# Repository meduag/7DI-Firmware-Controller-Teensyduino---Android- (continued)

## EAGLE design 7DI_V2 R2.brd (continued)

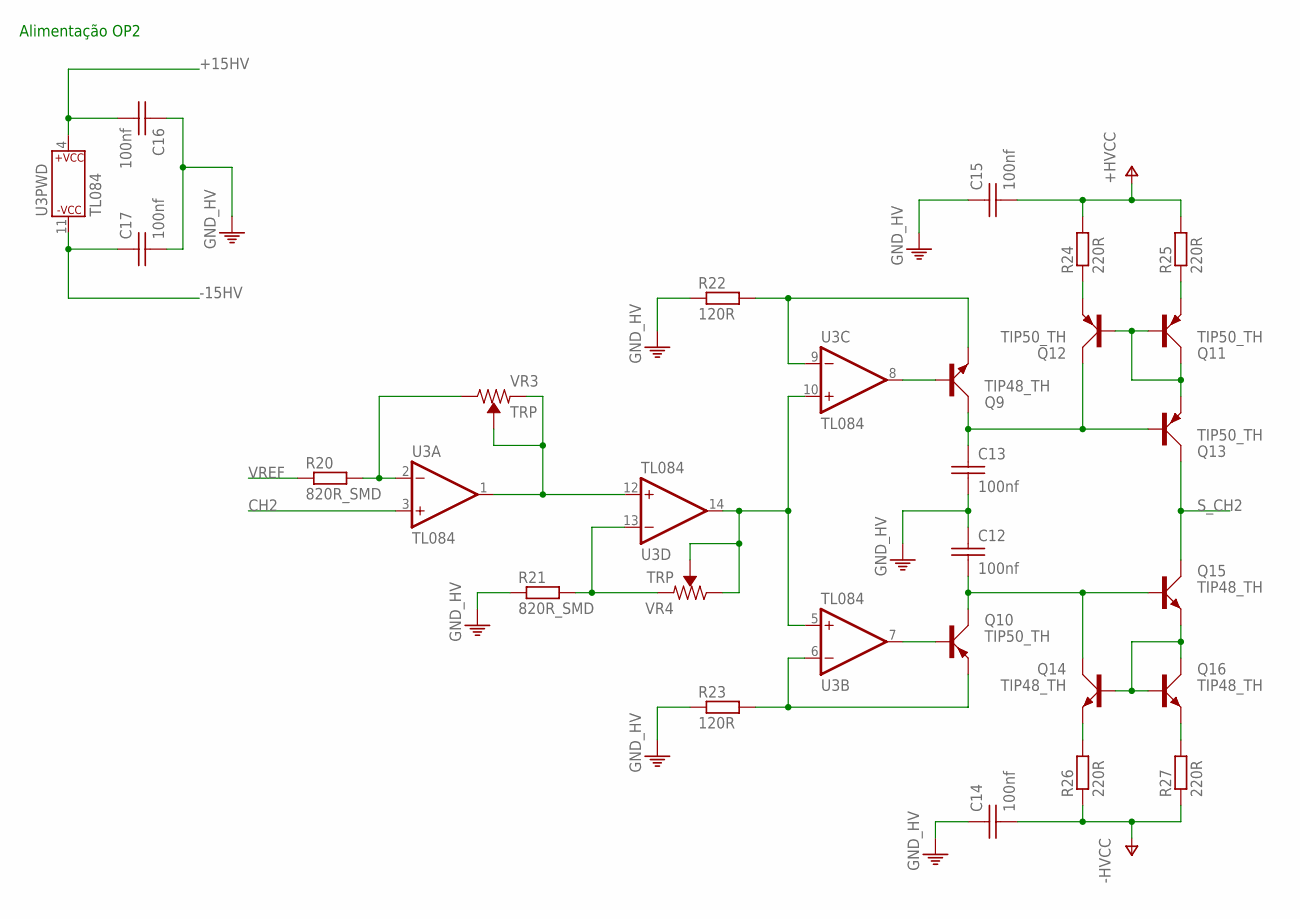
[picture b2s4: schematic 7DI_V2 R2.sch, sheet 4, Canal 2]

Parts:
C12, C13: 100nf; CAP_CER_2,54-5X5
C14, C15: 100nf; CAP_CER_16X7
C16, C17: 100nf; CAP_CER_SMD-0805
Q9, Q14, Q15, Q16: TIP48_TH; TO220
Q10, Q11, Q12, Q13: TIP50_TH; TO220
R20, R21: 820R_SMD; RESISTENCIA_0805
R22, R23: 120R; 0204V
R24, R25, R26, R27: 220R; 0204V
U3: TL084; SO14OP
VR3, VR4: TRP; TRIMPOT-PTH-3386U

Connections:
+15HV: C16.2, U3.4 (P$V+); also elsewhere on the board
-15HV: C17.1, U3.11 (P$V-); also elsewhere on the board
CH2: U3.3 (+IN); also elsewhere on the board
unnamed: R20.2, U3.2 (-IN), VR3.3 (CW)
unnamed: U3.1 (OUT), U3.12 (+IN), VR3.1 (CCW), VR3.2 (WIPER)
unnamed: U3.5 (+IN), U3.10 (+IN), U3.14 (OUT), VR4.2 (WIPER), VR4.3 (CW)
unnamed: R21.2, U3.13 (-IN), VR4.1 (CCW)
unnamed: Q9.E, R22.2, U3.9 (-IN)
unnamed: Q10.B, U3.7 (OUT)
unnamed: Q10.E, R23.2, U3.6 (-IN)
unnamed: C12.2, Q10.C, Q14.C, Q15.B
unnamed: C13.1, Q9.C, Q12.C, Q13.B
unnamed: Q12.E, R24.1
unnamed: Q11.E, R25.1
unnamed: Q11.B, Q11.C, Q12.B, Q13.E
unnamed: Q14.B, Q15.E, Q16.B, Q16.C
unnamed: Q14.E, R26.2
unnamed: Q16.E, R27.2
unnamed: Q9.B, U3.8 (OUT)
PE: C12.1, C13.2, C14.1, C15.1, C16.1, C17.2, R21.1, R22.1, R23.1; also elsewhere on the board
S_CH2: Q13.C, Q15.C; also elsewhere on the board
V+: C15.2, R24.2, R25.2; also elsewhere on the board
V-: C14.2, R26.1, R27.1; also elsewhere on the board
VREF: R20.1; also elsewhere on the board

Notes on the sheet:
Alimentação OP2

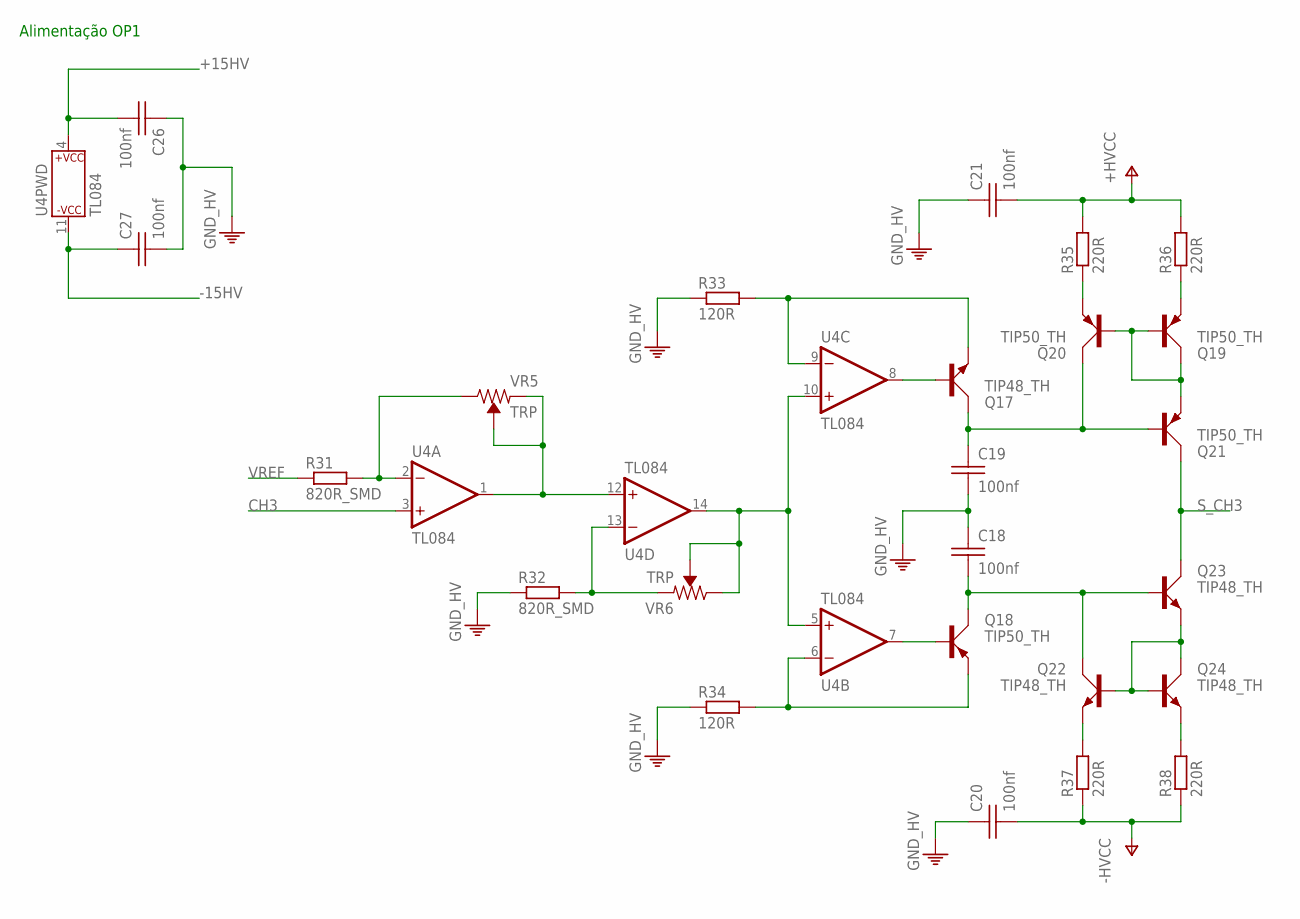
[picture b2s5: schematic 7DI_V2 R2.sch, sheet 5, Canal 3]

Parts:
C18, C19: 100nf; CAP_CER_2,54-5X5
C20, C21: 100nf; CAP_CER_16X7
C26, C27: 100nf; CAP_CER_SMD-0805
Q17, Q22, Q23, Q24: TIP48_TH; TO220
Q18, Q19, Q20, Q21: TIP50_TH; TO220
R31, R32: 820R_SMD; RESISTENCIA_0805
R33, R34: 120R; 0204V
R35, R36, R37, R38: 220R; 0204V
U4: TL084; SO14OP
VR5, VR6: TRP; TRIMPOT-PTH-3386U

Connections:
+15HV: C26.2, U4.4 (P$V+); also elsewhere on the board
-15HV: C27.1, U4.11 (P$V-); also elsewhere on the board
CH3: U4.3 (+IN); also elsewhere on the board
unnamed: R31.2, U4.2 (-IN), VR5.3 (CW)
unnamed: U4.1 (OUT), U4.12 (+IN), VR5.1 (CCW), VR5.2 (WIPER)
unnamed: U4.5 (+IN), U4.10 (+IN), U4.14 (OUT), VR6.2 (WIPER), VR6.3 (CW)
unnamed: R32.2, U4.13 (-IN), VR6.1 (CCW)
unnamed: Q17.E, R33.2, U4.9 (-IN)
unnamed: Q18.B, U4.7 (OUT)
unnamed: Q18.E, R34.2, U4.6 (-IN)
unnamed: C18.2, Q18.C, Q22.C, Q23.B
unnamed: C19.1, Q17.C, Q20.C, Q21.B
unnamed: Q20.E, R35.1
unnamed: Q19.E, R36.1
unnamed: Q19.B, Q19.C, Q20.B, Q21.E
unnamed: Q22.B, Q23.E, Q24.B, Q24.C
unnamed: Q22.E, R37.2
unnamed: Q24.E, R38.2
unnamed: Q17.B, U4.8 (OUT)
PE: C18.1, C19.2, C20.1, C21.1, C26.1, C27.2, R32.1, R33.1, R34.1; also elsewhere on the board
S_CH3: Q21.C, Q23.C; also elsewhere on the board
V+: C21.2, R35.2, R36.2; also elsewhere on the board
V-: C20.2, R37.1, R38.1; also elsewhere on the board
VREF: R31.1; also elsewhere on the board

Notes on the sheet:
Alimentação OP1

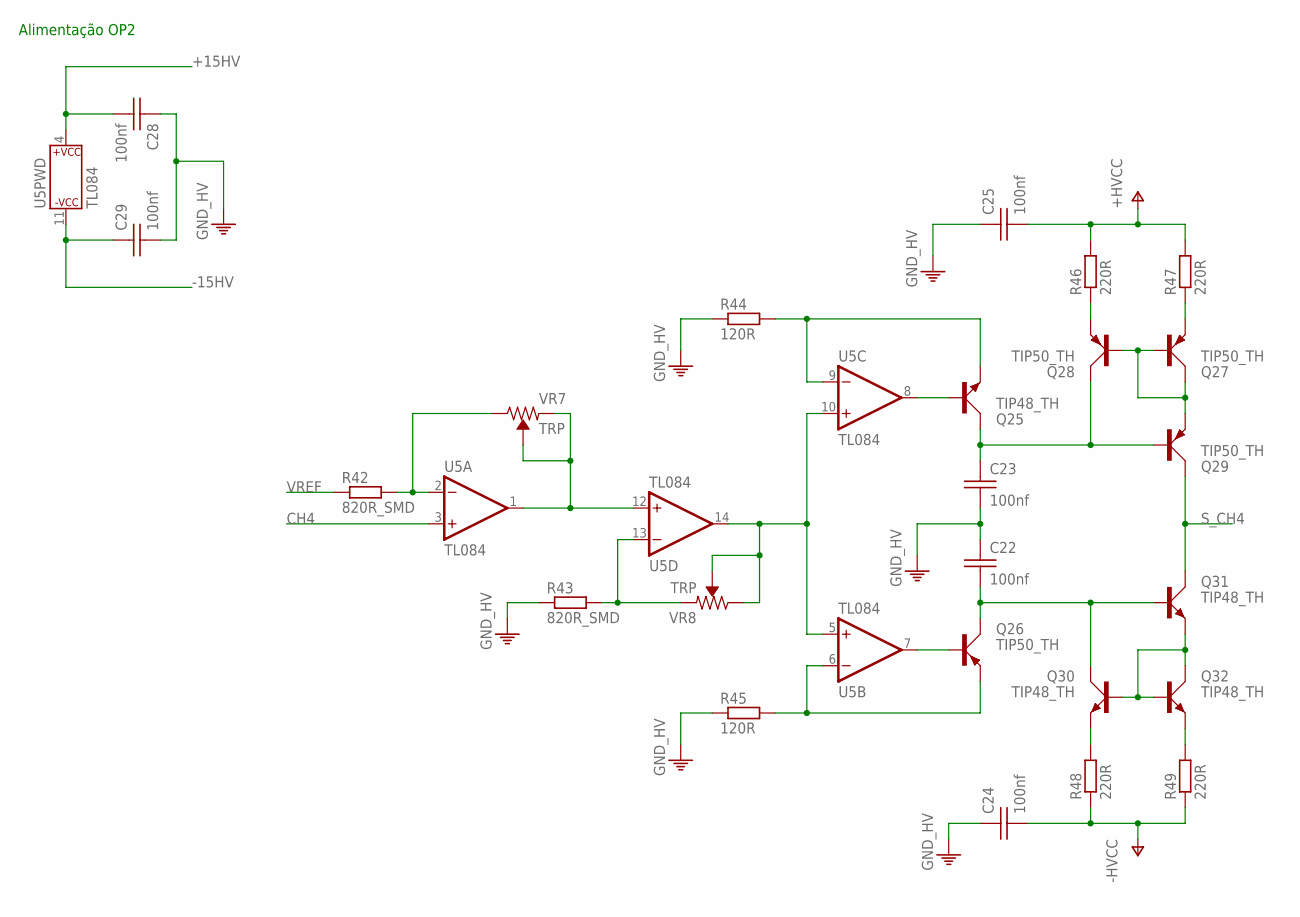
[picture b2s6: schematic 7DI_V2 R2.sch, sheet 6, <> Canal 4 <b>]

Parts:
C22, C23: 100nf; CAP_CER_2,54-5X5
C24, C25: 100nf; CAP_CER_16X7
C28, C29: 100nf; CAP_CER_SMD-0805
Q25, Q30, Q31, Q32: TIP48_TH; TO220
Q26, Q27, Q28, Q29: TIP50_TH; TO220
R42, R43: 820R_SMD; RESISTENCIA_0805
R44, R45: 120R; 0204V
R46, R47, R48, R49: 220R; 0204V
U5: TL084; SO14OP
VR7, VR8: TRP; TRIMPOT-PTH-3386U

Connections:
+15HV: C28.2, U5.4 (P$V+); also elsewhere on the board
-15HV: C29.1, U5.11 (P$V-); also elsewhere on the board
CH4: U5.3 (+IN); also elsewhere on the board
unnamed: R42.2, U5.2 (-IN), VR7.3 (CW)
unnamed: U5.1 (OUT), U5.12 (+IN), VR7.1 (CCW), VR7.2 (WIPER)
unnamed: U5.5 (+IN), U5.10 (+IN), U5.14 (OUT), VR8.2 (WIPER), VR8.3 (CW)
unnamed: R43.2, U5.13 (-IN), VR8.1 (CCW)
unnamed: Q25.E, R44.2, U5.9 (-IN)
unnamed: Q26.B, U5.7 (OUT)
unnamed: Q26.E, R45.2, U5.6 (-IN)
unnamed: C22.2, Q26.C, Q30.C, Q31.B
unnamed: C23.1, Q25.C, Q28.C, Q29.B
unnamed: Q28.E, R46.1
unnamed: Q27.E, R47.1
unnamed: Q27.B, Q27.C, Q28.B, Q29.E
unnamed: Q30.B, Q31.E, Q32.B, Q32.C
unnamed: Q30.E, R48.2
unnamed: Q32.E, R49.2
unnamed: Q25.B, U5.8 (OUT)
PE: C22.1, C23.2, C24.1, C25.1, C28.1, C29.2, R43.1, R44.1, R45.1; also elsewhere on the board
S_CH4: Q29.C, Q31.C; also elsewhere on the board
V+: C25.2, R46.2, R47.2; also elsewhere on the board
V-: C24.2, R48.1, R49.1; also elsewhere on the board
VREF: R42.1; also elsewhere on the board

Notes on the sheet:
Alimentação OP2

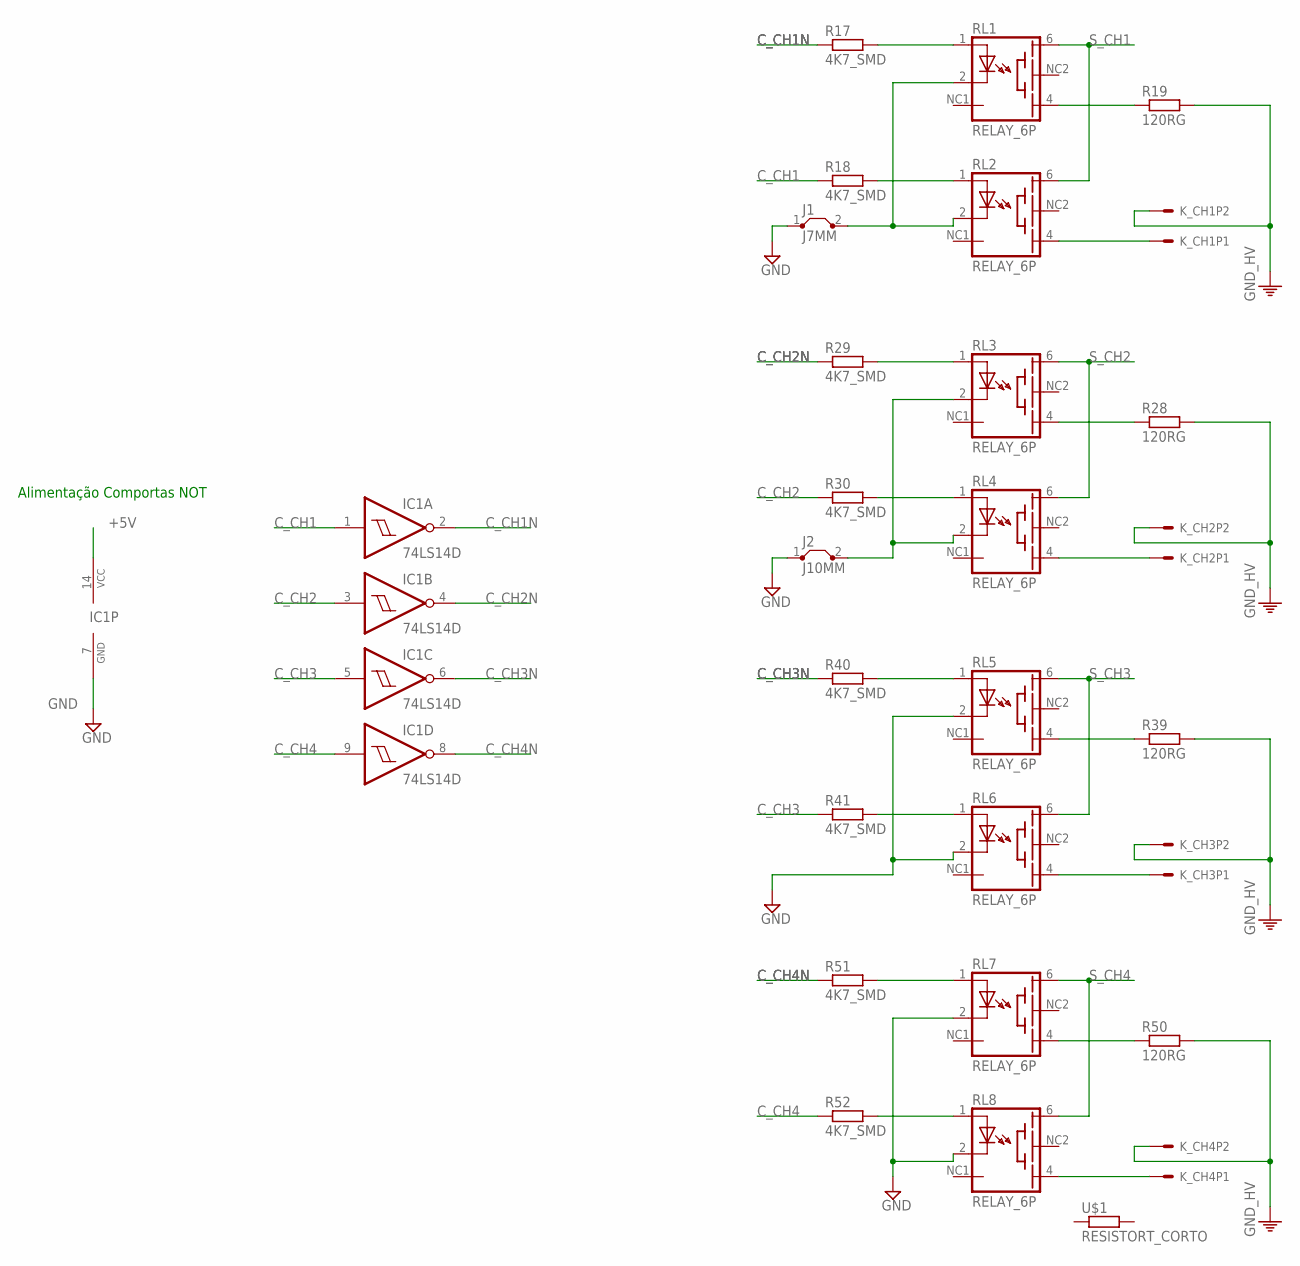
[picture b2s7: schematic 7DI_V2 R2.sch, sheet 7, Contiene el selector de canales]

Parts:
IC1: 74LS14D; SO14NOT
J1: J7MM; 07
J2: J10MM; 10
K_CH1, K_CH2, K_CH3, K_CH4: CONECTOR_5.08; CONECTOR_X2_5.08
R17, R18, R29, R30, R40, R41, R51, R52: 4K7_SMD; RESISTENCIA_0805
R19, R28, R39, R50: 120RG; 0617V
RL1, RL2, RL3, RL4, RL5, RL6, RL7, RL8: RELAY_6P; TS210
U$1: RESISTORT_CORTO; 0204V

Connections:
+5V: IC1.14 (VCC); also elsewhere on the board
C_CH1: IC1.1 (I), R18.1; also elsewhere on the board
C_CH1N: IC1.2 (O), R17.1
C_CH2: IC1.3 (I), R30.1; also elsewhere on the board
C_CH2N: IC1.4 (O), R29.1
C_CH3: IC1.5 (I), R41.1; also elsewhere on the board
C_CH3N: IC1.6 (O), R40.1
C_CH4: IC1.9 (I), R52.1; also elsewhere on the board
C_CH4N: IC1.8 (O), R51.1
GND: IC1.7 (GND), J1.1, J2.1, RL5.2 (C), RL6.2 (C), RL7.2 (C), RL8.2 (C); also elsewhere on the board
unnamed: R17.2, RL1.1 (A)
unnamed: R18.2, RL2.1 (A)
unnamed: R19.1, RL1.4 (EMI)
unnamed: K_CH1.1, RL2.4 (EMI)
unnamed: R29.2, RL3.1 (A)
unnamed: R30.2, RL4.1 (A)
unnamed: R28.1, RL3.4 (EMI)
unnamed: K_CH2.1, RL4.4 (EMI)
unnamed: R40.2, RL5.1 (A)
unnamed: R41.2, RL6.1 (A)
unnamed: R39.1, RL5.4 (EMI)
unnamed: K_CH3.1, RL6.4 (EMI)
unnamed: R51.2, RL7.1 (A)
unnamed: R52.2, RL8.1 (A)
unnamed: R50.1, RL7.4 (EMI)
unnamed: K_CH4.1, RL8.4 (EMI)
unnamed: J1.2, RL1.2 (C), RL2.2 (C)
unnamed: J2.2, RL3.2 (C), RL4.2 (C)
PE: K_CH1.2, K_CH2.2, K_CH3.2, K_CH4.2, R19.2, R28.2, R39.2, R50.2; also elsewhere on the board
S_CH1: RL1.6 (BAS), RL2.6 (BAS); also elsewhere on the board
S_CH2: RL3.6 (BAS), RL4.6 (BAS); also elsewhere on the board
S_CH3: RL5.6 (BAS), RL6.6 (BAS); also elsewhere on the board
S_CH4: RL7.6 (BAS), RL8.6 (BAS); also elsewhere on the board

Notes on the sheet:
Alimentação Comportas NOT

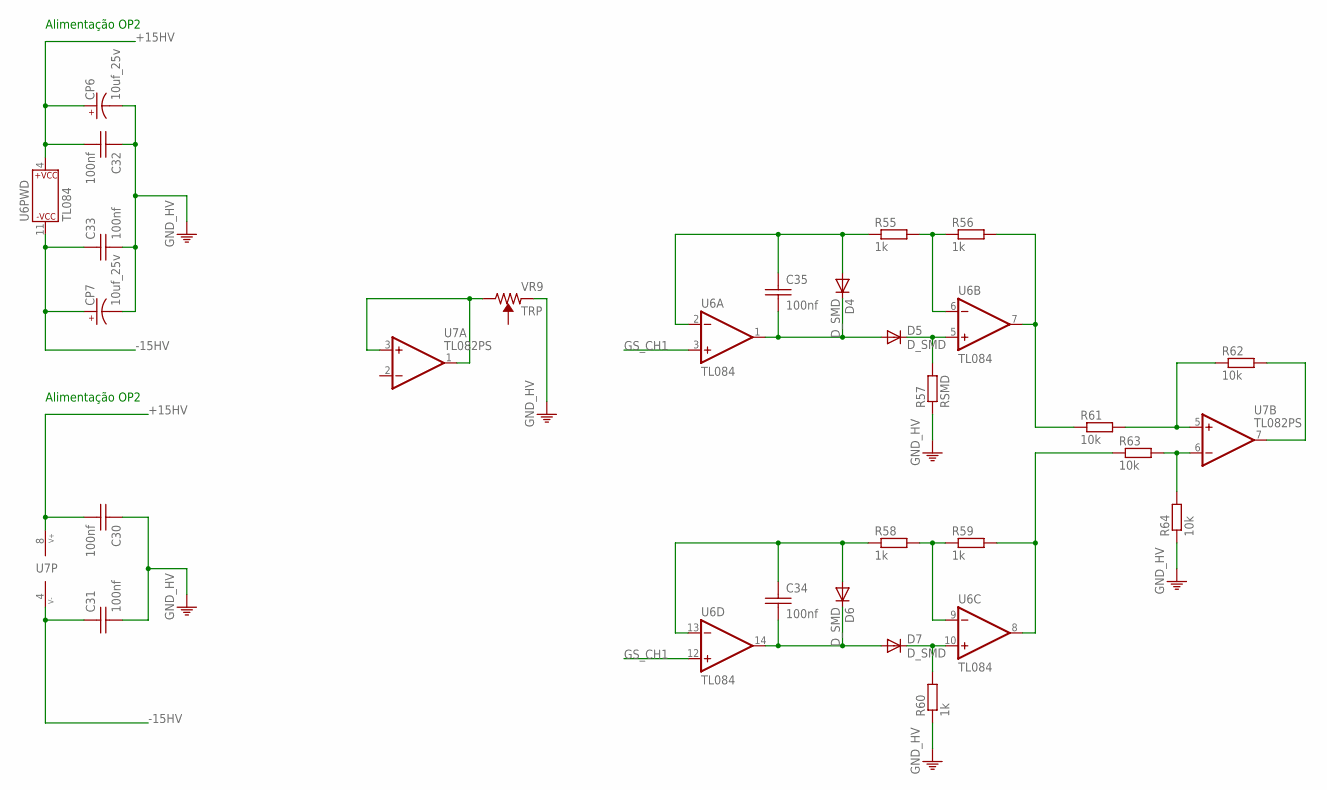
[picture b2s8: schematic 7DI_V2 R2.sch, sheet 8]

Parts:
C30, C31, C32, C33, C34, C35: 100nf; CAP_CER_SMD-0805
CP6, CP7: 10uf_25v; CAP_T_2,5-D5
D4, D5, D6, D7: D_SMD
R55, R56, R58, R59, R60: 1k; RESISTENCIA_0805
R57: RSMD; RESISTENCIA_0805
R61, R62, R63, R64: 10k; RESISTENCIA_0805
U6: TL084; SO14OP
U7: TL082PS; SOP08
VR9: TRP; TRIMPOT-PTH-3386U

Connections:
+15HV: C30.2, C32.2, CP6.+, U6.4 (P$V+), U7.8 (V+); also elsewhere on the board
-15HV: C31.1, C33.1, CP7.+, U6.11 (P$V-), U7.4 (V-); also elsewhere on the board
GS_CH1: U6.3 (+IN), U6.12 (+IN); also elsewhere on the board
unnamed: C35.2, D4.K (C), D5.A, U6.1 (OUT)
unnamed: C35.1, D4.A, R55.1, U6.2 (-IN)
unnamed: D5.K (C), R57.2, U6.5 (+IN)
unnamed: R55.2, R56.1, U6.6 (-IN)
unnamed: R56.2, R61.1, U6.7 (OUT)
unnamed: C34.2, D6.K (C), D7.A, U6.14 (OUT)
unnamed: C34.1, D6.A, R58.1, U6.13 (-IN)
unnamed: D7.K (C), R60.2, U6.10 (+IN)
unnamed: R58.2, R59.1, U6.9 (-IN)
unnamed: R59.2, R63.1, U6.8 (OUT)
unnamed: R61.2, R62.1, U7.5 (+IN)
unnamed: R62.2, U7.7 (OUT)
unnamed: R63.2, R64.2, U7.6 (-IN)
unnamed: U7.1 (OUT), U7.3 (+IN), VR9.3 (CW)
PE: C30.1, C31.2, C32.1, C33.2, CP6.-, CP7.-, R57.1, R60.1, R64.1, VR9.1 (CCW); also elsewhere on the board

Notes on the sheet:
Alimentação OP2

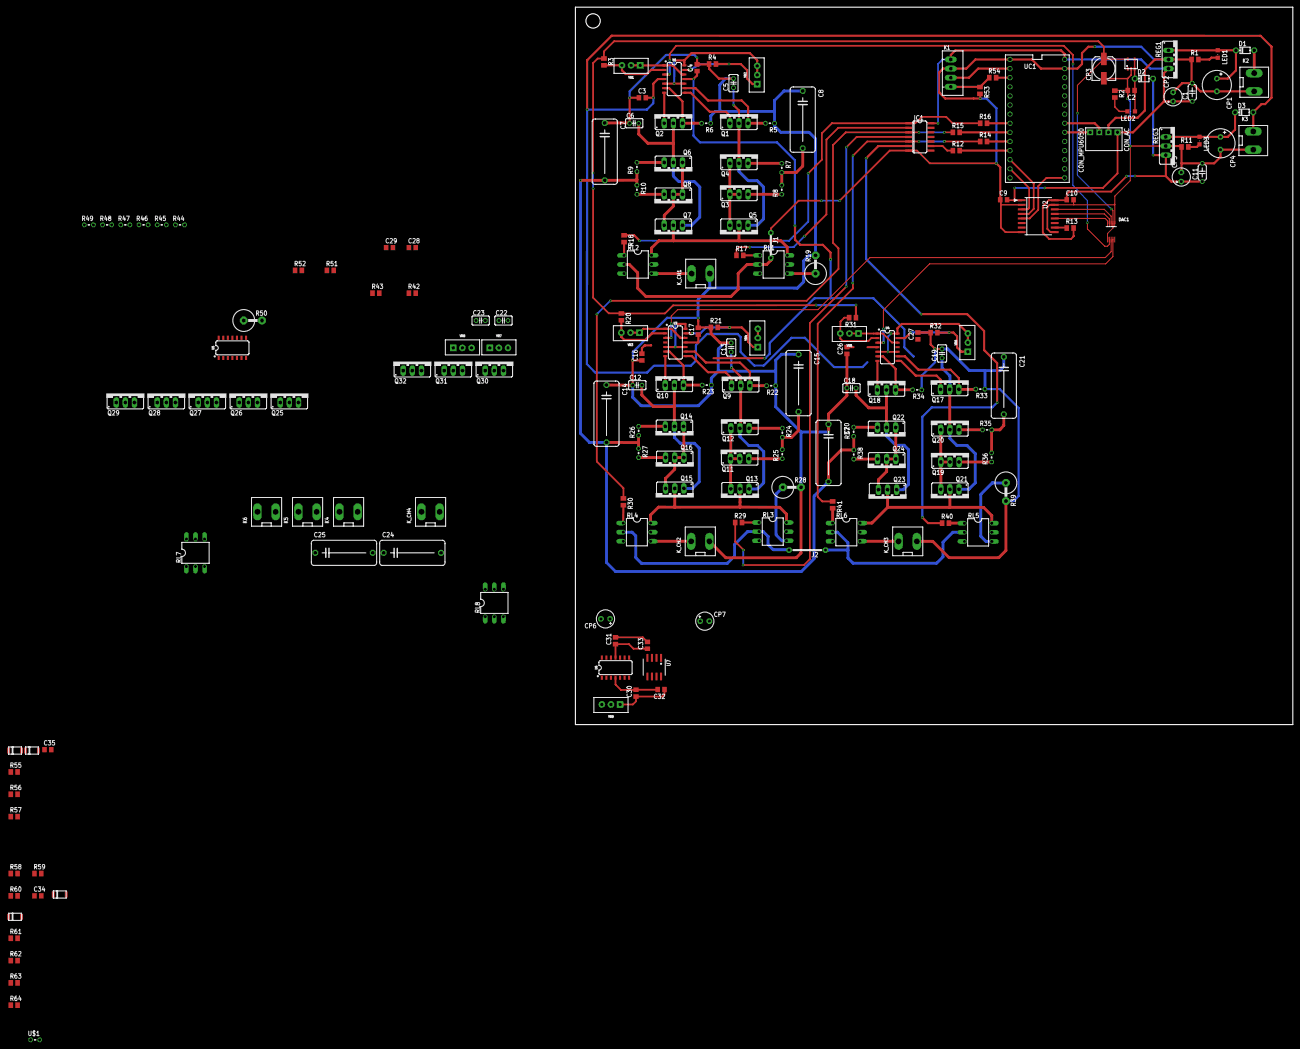
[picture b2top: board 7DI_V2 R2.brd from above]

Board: 2 copper layers, 200.0 x 200.0 mm, 192 parts (0 on the bottom side), 144 nets.

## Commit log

2018-01-27 Esquemático en evolución
    hasta aquí en esta versión falta colocar la comprobación del final del canal
2018-01-27 PCB
    apenas en la version 2
2018-04-10 Versão com correções
    A partir das versões anteriores foram feitas mudanças no PBC e no esquemático
2018-04-10 codigo com 50% para testar funcionamento
